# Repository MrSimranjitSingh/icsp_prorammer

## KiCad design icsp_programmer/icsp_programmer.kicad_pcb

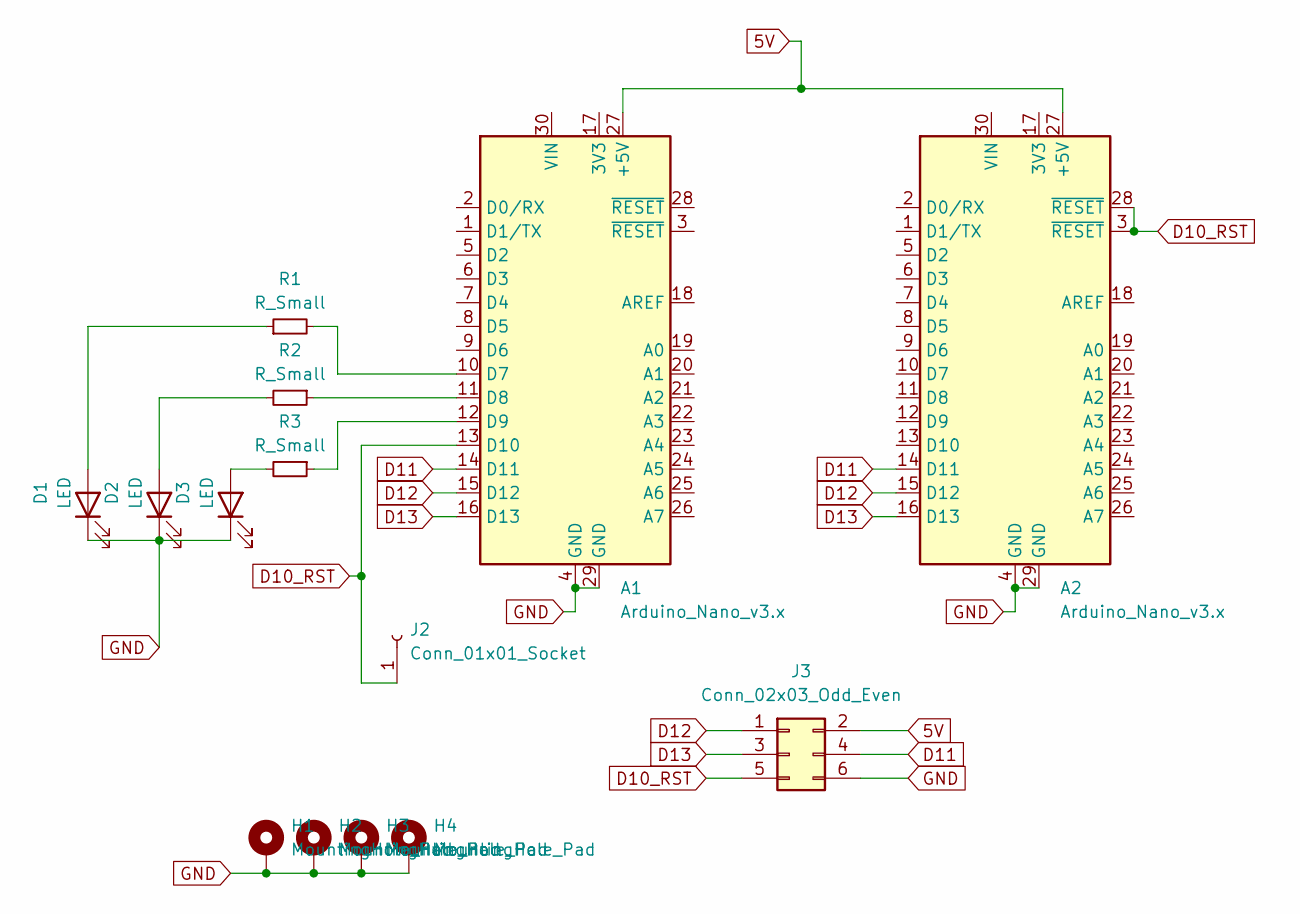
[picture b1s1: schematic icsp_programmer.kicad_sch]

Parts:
A1, A2: Arduino_Nano_v3.x; Arduino_Nano
D1, D2, D3: LED; LED_D5.0mm
H1, H2, H3, H4: MountingHole_Pad; MountingHole_3.2mm_M3_Pad
J2: Conn_01x01_Socket; PinHeader_1x01_P2.54mm_Vertical
J3: Conn_02x03_Odd_Even; PinHeader_2x03_P2.54mm_Vertical
R1, R2, R3: R_Small; R_Axial_DIN0207_L6.3mm_D2.5mm_P7.62mm_Horizontal

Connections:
5V: A1.27 (+5V), A2.27 (+5V), J3.2
D10_RST: A1.13 (D10), A2.3 (~RESET), A2.28 (~RESET), J2.1, J3.5
D11: A1.14 (D11), A2.14 (D11), J3.4
D12: A1.15 (D12), A2.15 (D12), J3.1
D13: A1.16 (D13), A2.16 (D13), J3.3
GND: A1.4 (GND), A1.29 (GND), A2.4 (GND), A2.29 (GND), D1.1 (K), D2.1 (K), D3.1 (K), H1.1, H2.1, H3.1, H4.1, J3.6
unnamed: A1.10 (D7), R1.2
unnamed: A1.11 (D8), R2.1
unnamed: A1.12 (D9), R3.1
unnamed: D1.2 (A), R1.1
unnamed: D2.2 (A), R2.2
unnamed: D3.2 (A), R3.2

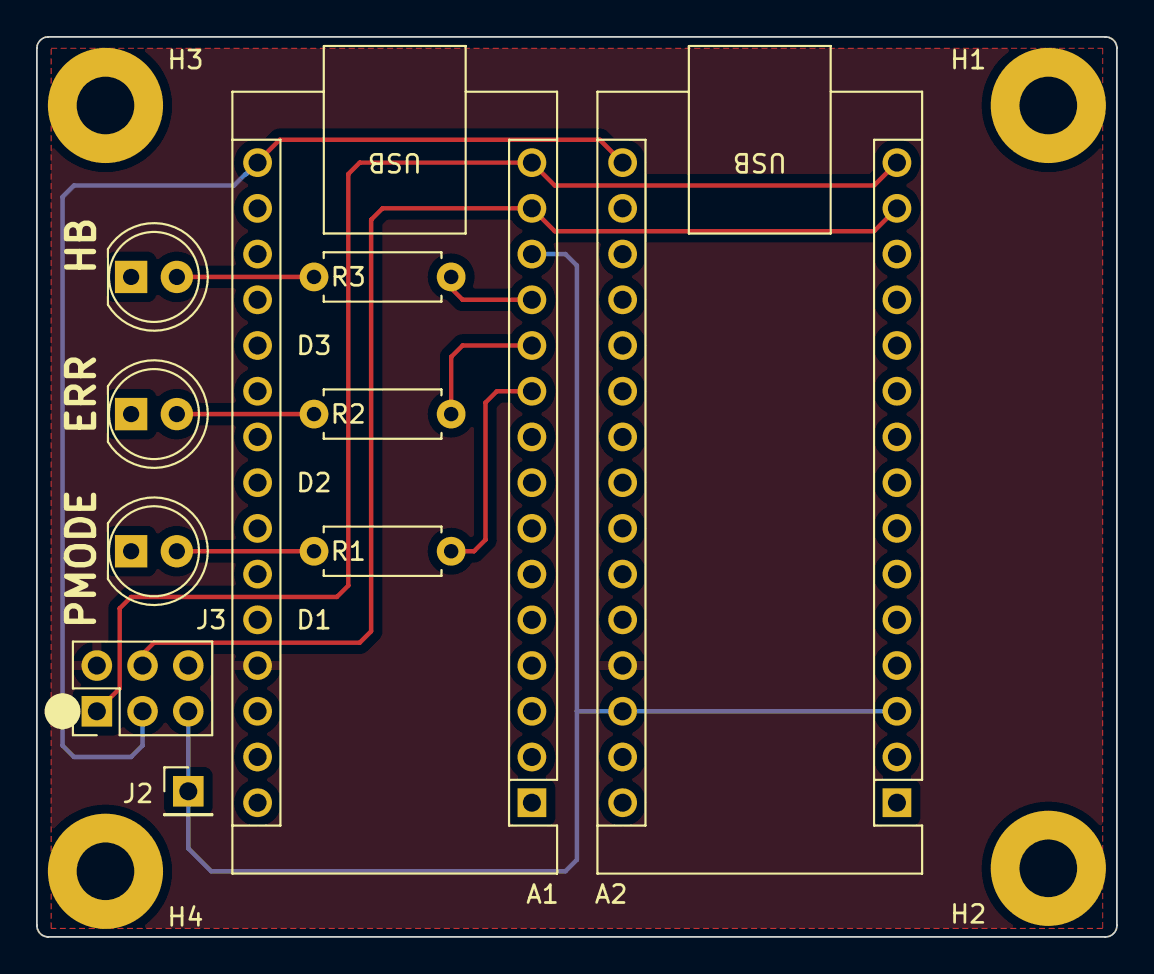
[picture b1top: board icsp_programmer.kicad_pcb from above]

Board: 2 copper layers, 60.0 x 50.0 mm, 14 parts (0 on the bottom side), 12 nets.
